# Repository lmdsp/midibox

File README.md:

# Midibox PCBs

A collection of schematics and printed circuit board layouts for various [Midibox NG](http://www.ucapps.de/midibox_ng.html) modules,
made with [KiCAD](https://kicad.org/).
The designs were made with MCU style MIDI control surfaces in mind, but could also be useful for other applications.

- [Midibox PCBs](#midibox-pcbs)
  - [OLED carrier board](#oled-carrier-board)
    - [Bill of materials](#bill-of-materials)
    - [Assembly](#assembly)
    - [Connections](#connections)
      - [Internal power](#internal-power)
      - [External power](#external-power)
      - [PCB top side / OLED pin headers](#pcb-top-side--oled-pin-headers)
      - [PCB bottom side / other components](#pcb-bottom-side--other-components)
  - [TODO](#todo)

## OLED carrier board

Holds eight 0.96″ OLED screens, spaced by 1.2″ for a compact design.

Only 4-wire SPI, 7-pin OLED types are supported.
Be sure to check the dimensions and pinout matches before purchase!

Optional decoupling 100nF caps `C1`-`C8` can be stuffed to improve noise rejection in case of flickering or other issues.

### Bill of materials

- OLED screen x 8
- 10k 1/4W resistor
- 10µF/35V radial capacitor
- 2x8 box connector socket
- 2x8 box headers x 2
- 16-way cable
- 7-pin sockets x 8 (0.1″ spacing, for the OLEDs)
- 3-pin header
- 2-pin jumper
- 100nF ceramic capacitor x 8 (optional)

### Assembly

1. Solder the sockets for the OLEDs on the top side
2. Solder all other components on the bottom side
3. Connect `J2` to `core/J15A` using a ribbon cable
4. Configure the software

### Connections

`J1` connects to `J15A` of the [STM32F4 core](http://www.ucapps.de/mbhp_core_stm32f4.html).

#### Internal power

`J15_S` should be set to 3.3V on the core, and `JP1` to _Core_ on this PCB.

#### External power

The LDO regulator on the core board can only supply 100mA.
Therefore this PCB has an option to use external 3.3V power through `J2`.
In this case `JP1` should be set to _Ext_.

#### PCB top side / OLED pin headers

----

----

#### PCB bottom side / other components

----

## TODO

- Software configuration
- Secure OLED mechanically
- Photos of PCB and working displays

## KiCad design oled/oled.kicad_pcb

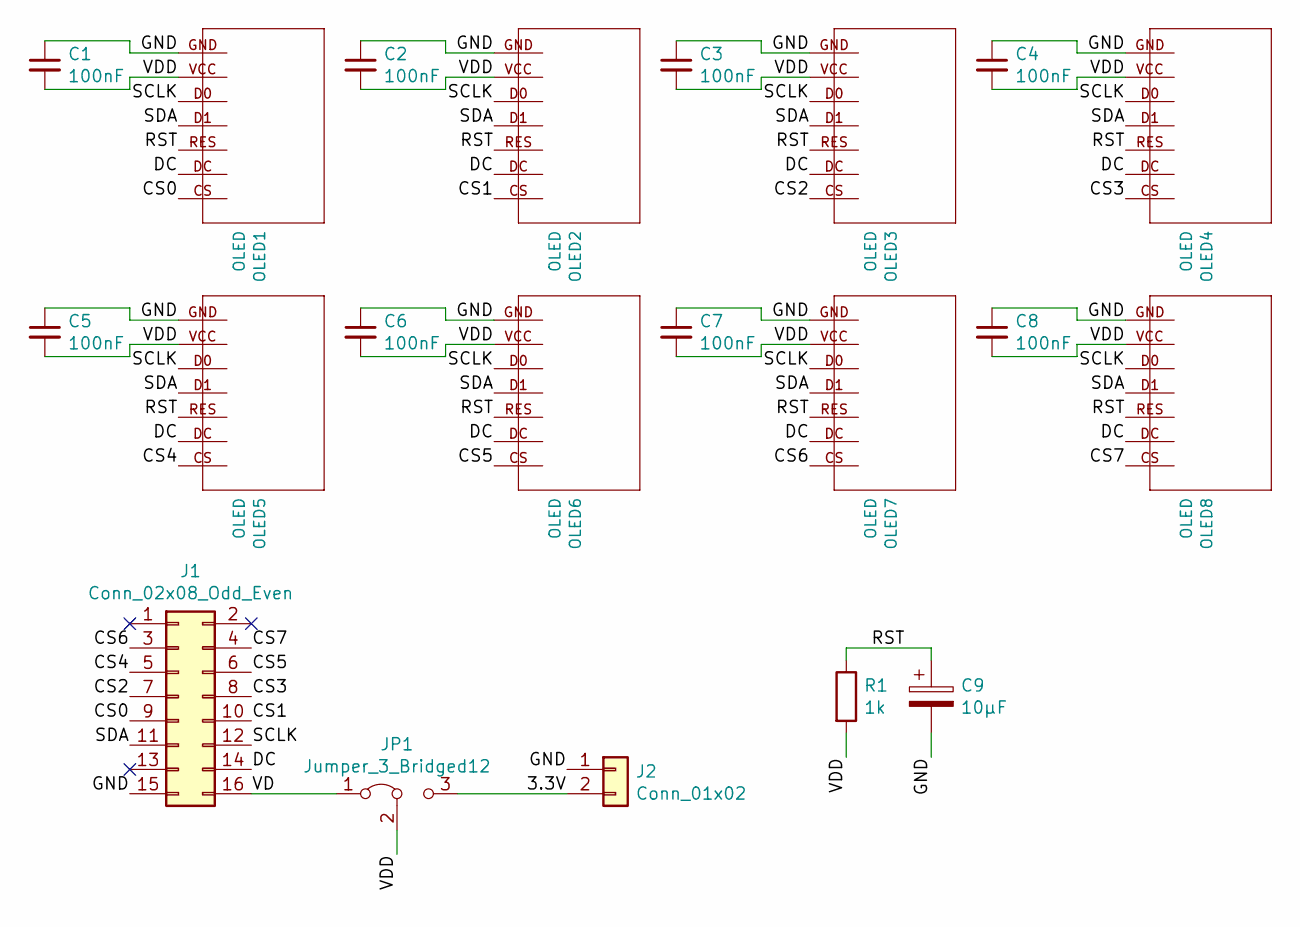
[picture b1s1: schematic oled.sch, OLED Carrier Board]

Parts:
C1, C2, C3, C4, C5, C6, C7, C8: 100nF; C_Disc_D3.0mm_W2.0mm_P2.50mm
C9: 10µF; CP_Radial_D5.0mm_P2.50mm
J1: Conn_02x08_Odd_Even; IDC-Header_2x08_P2.54mm_Vertical
J2: Conn_01x02; Molex_KK-254_AE-6410-02A_1x02_P2.54mm_Vertical
JP1: Jumper_3_Bridged12; PinHeader_1x03_P2.54mm_Vertical
OLED1, OLED2, OLED3, OLED4, OLED5, OLED6, OLED7, OLED8: OLED; oled-128x64-4spi-0.96
R1: 1k; R_Axial_DIN0207_L6.3mm_D2.5mm_P7.62mm_Horizontal

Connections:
/3.3V: J2.2, JP1.3 (B)
/CS0: J1.9, OLED1.CS
/CS1: J1.10, OLED2.CS
/CS2: J1.7, OLED3.CS
/CS3: J1.8, OLED4.CS
/CS4: J1.5, OLED5.CS
/CS5: J1.6, OLED6.CS
/CS6: J1.3, OLED7.CS
/CS7: J1.4, OLED8.CS
/DC: J1.14, OLED1.DC, OLED2.DC, OLED3.DC, OLED4.DC, OLED5.DC, OLED6.DC, OLED7.DC, OLED8.DC
/GND: C1.1, C2.1, C3.1, C4.1, C5.1, C6.1, C7.1, C8.1, C9.2, J1.15, J2.1, OLED1.GND, OLED2.GND, OLED3.GND, OLED4.GND, OLED5.GND, OLED6.GND, OLED7.GND, OLED8.GND
/RST: C9.1, OLED1.RES, OLED2.RES, OLED3.RES, OLED4.RES, OLED5.RES, OLED6.RES, OLED7.RES, OLED8.RES, R1.1
/SCLK: J1.12, OLED1.D0, OLED2.D0, OLED3.D0, OLED4.D0, OLED5.D0, OLED6.D0, OLED7.D0, OLED8.D0
/SDA: J1.11, OLED1.D1, OLED2.D1, OLED3.D1, OLED4.D1, OLED5.D1, OLED6.D1, OLED7.D1, OLED8.D1
/VD: J1.16, JP1.1 (A)
/VDD: C1.2, C2.2, C3.2, C4.2, C5.2, C6.2, C7.2, C8.2, JP1.2 (C), OLED1.VCC, OLED2.VCC, OLED3.VCC, OLED4.VCC, OLED5.VCC, OLED6.VCC, OLED7.VCC, OLED8.VCC, R1.2

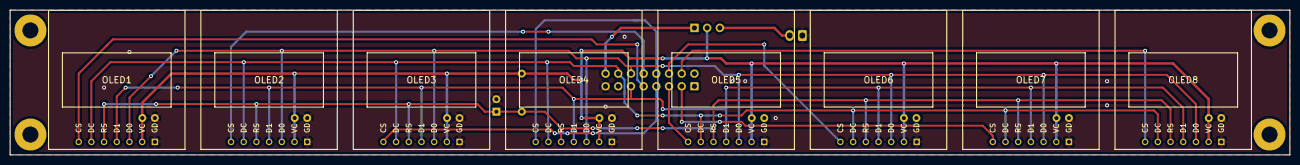
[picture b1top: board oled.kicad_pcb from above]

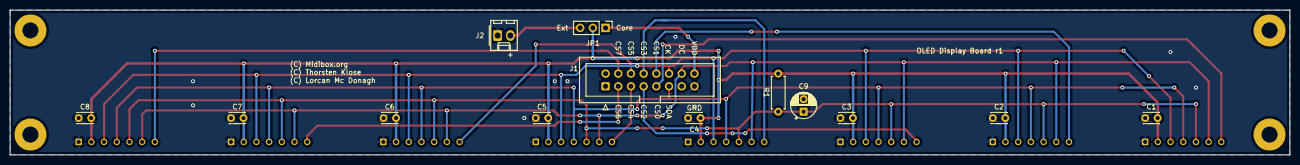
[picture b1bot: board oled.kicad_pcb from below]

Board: 2 copper layers, 256.0 x 29.0 mm, 21 parts (13 on the bottom side), 16 nets.

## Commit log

2021-04-16 OLED PCBs
2021-04-16 OLED readme
2021-04-16 Readme
2023-01-10 Create LICENSE
    Add license
2023-01-10 Rename LICENSE to LICENSE.md
